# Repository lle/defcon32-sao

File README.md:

## Firmware Structure
See this readme in this repo: [SAO31](https://github.com/lle/defcon31-addon)
The foundation firmware is from my SAO from last year. This year's firmware adds an the Racing game mode in addition to the animation/screensaver mode.

## How to Flash
Things you need:
* ST-Link - I personally use an STM32F0 Nucleo Board: [497-15096-ND](https://www.digikey.ca/en/products/detail/stmicroelectronics/NUCLEO-F072RB/5047984)
* Female Connector: [H2193-ND](https://www.digikey.ca/en/products/detail/hirose-electric-co-ltd/DF13-4P-1-25DSA/241767?s=N4IgTCBcDaIBJgIwE4DMBaAcgERAXQF8g)
* Male Connector: [H2181-ND](https://www.digikey.ca/en/products/detail/hirose-electric-co-ltd/DF13-4S-1-25C/241750)
* Precrimped wires x4: [H4BXG-10112-B8-ND](https://www.digikey.ca/en/products/detail/hirose-electric-co-ltd/H4BXG-10112-B8/426117)

### Instruction
* Connect the ST-Link SWD header to the PCB's programming port

* Compile the code in STM CubeIDE: "Project"->"Build All"
* Connect your Nucleo board to your computer
* Configure the debugger as follows: "Run" -> "Debug Configurations"

* Flash the firmware: "Run" -> "Run"
* You will see this in the logs
```
Memory Programming ...
Opening and parsing file: ST-LINK_GDB_server_a15460.srec
  File          : ST-LINK_GDB_server_a15460.srec
  Size          : 21.34 KB 
  Address       : 0x08000000 
Erasing memory corresponding to segment 0:
Erasing internal memory sectors [0 21]
Download in Progress:
File download complete
Time elapsed during download operation: 00:00:01.454
Verifying ...
Download verified successfully 
Shutting down...
Exit.
```
https://github.com/lle/defcon31-addon

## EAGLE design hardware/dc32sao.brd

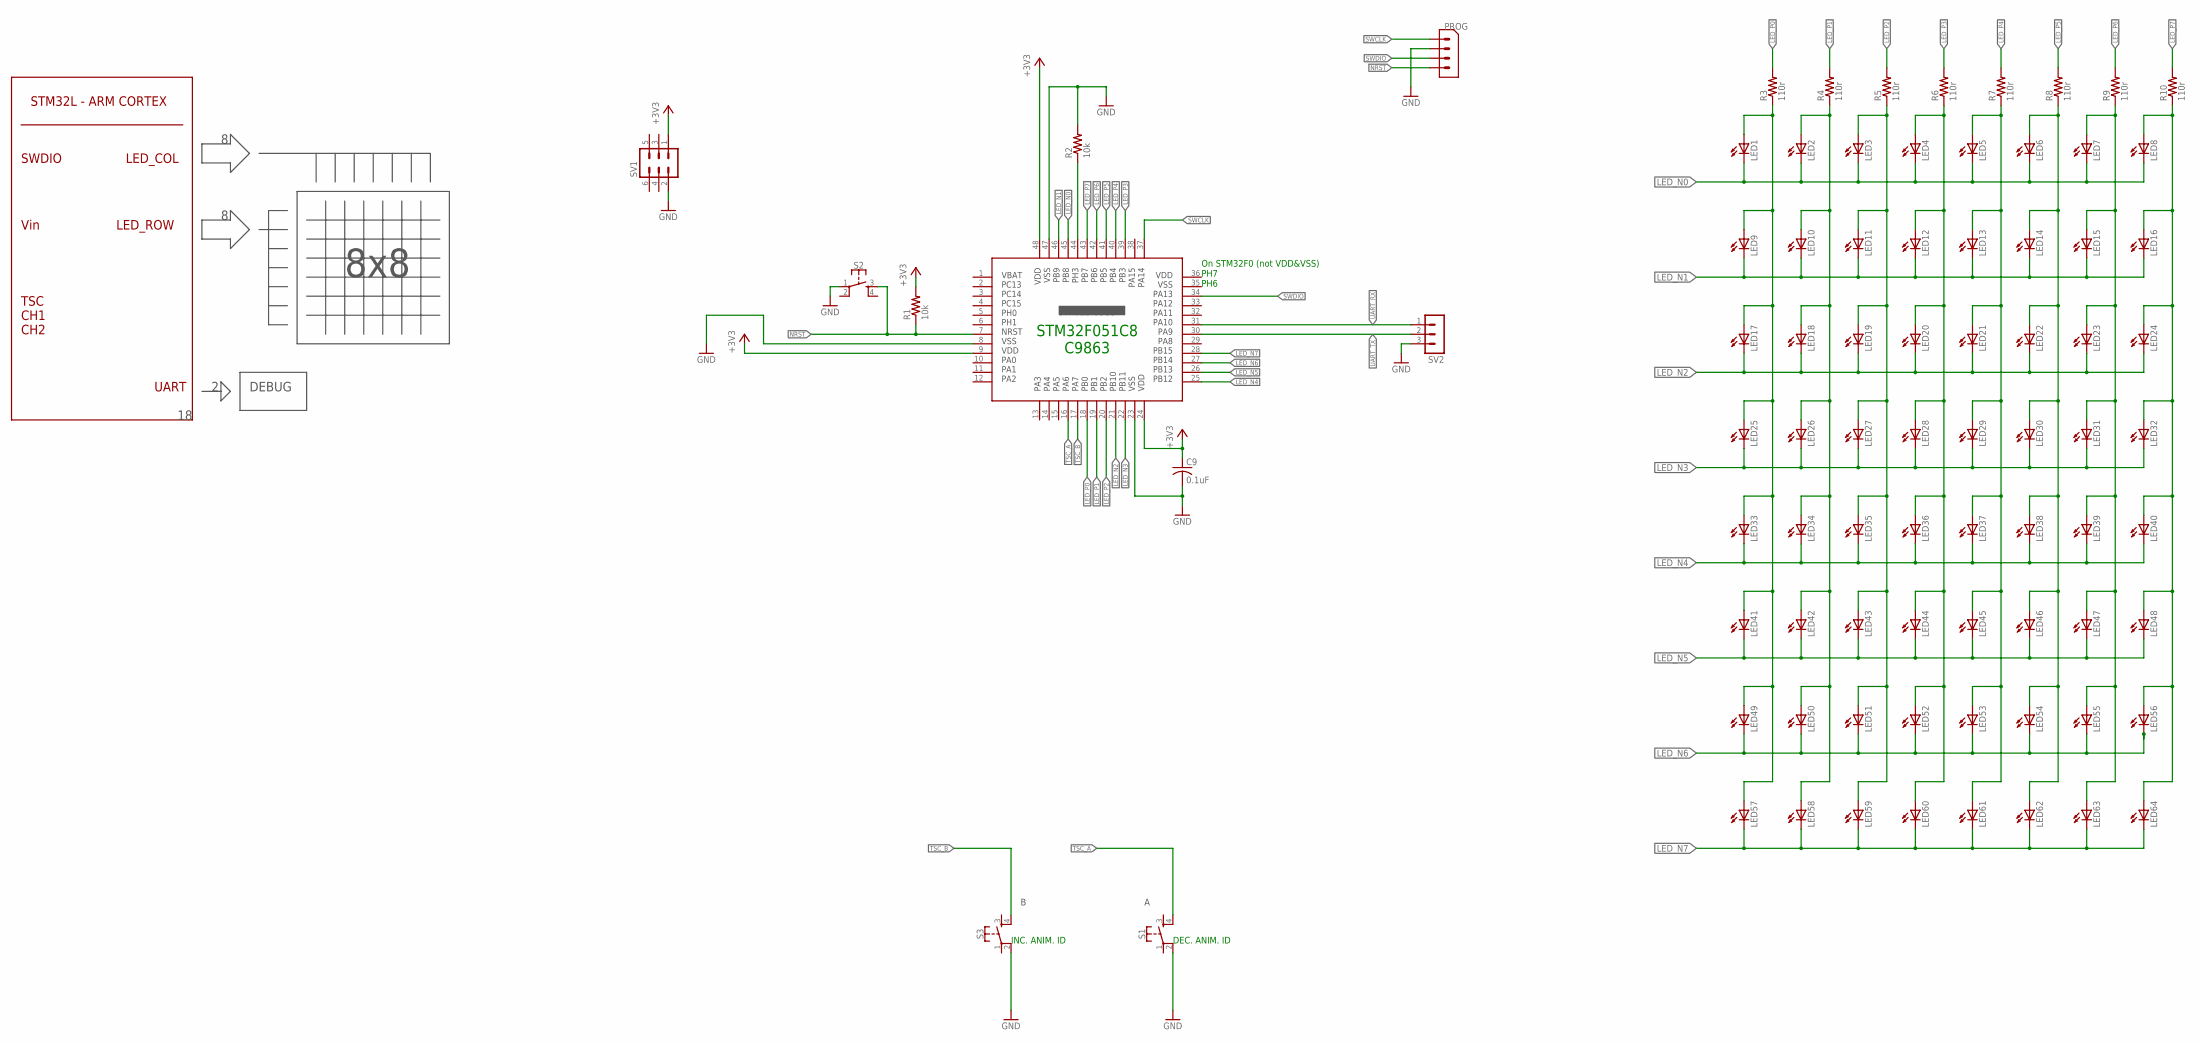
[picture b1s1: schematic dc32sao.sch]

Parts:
C9: 0.1uF; C0603
LED1, LED2, LED3, LED4, LED5, LED6, LED7, LED8, LED9, LED10, LED11, LED12, LED13, LED14, LED15, LED16, LED17, LED18, LED19, LED20, LED21, LED22, LED23, LED24, LED25, LED26, LED27, LED28, LED29, LED30, LED31, LED32, LED33, LED34, LED35, LED36, LED37, LED38, LED39, LED40, LED41, LED42, LED43, LED44, LED45, LED46, LED47, LED48, LED49, LED50, LED51, LED52, LED53, LED54, LED55, LED56, LED57, LED58, LED59, LED60, LED61, LED62, LED63, LED64: LEDCHIP-LED0603; CHIP-LED0603
PROG: 4-PIN-1.25MM
R1, R2: 10k; R0603
R3, R4, R5, R6, R7, R8, R9, R10: 110r; R0603
S1, S2, S3: MOMENTARY-SWITCH-SPST-2-SMD-5.2MM; TACTILE_SWITCH_SMD_5.2MM
SV1: MA03-2
SV2: MA03-1
U$2: STM32L431CC; QFP50P900X900X160-48

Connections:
+3V3: C9.1, R1.2, SV1.1, U$2.9, U$2.24, U$2.48
GND: C9.2, PROG.P$3 (2), R2.2, S1.2, S2.1, S3.2, SV1.2, SV2.3, U$2.8, U$2.23, U$2.47
LED_N0: LED1.C, LED2.C, LED3.C, LED4.C, LED5.C, LED6.C, LED7.C, LED8.C, U$2.45
LED_N1: LED9.C, LED10.C, LED11.C, LED12.C, LED13.C, LED14.C, LED15.C, LED16.C, U$2.46
LED_N2: LED17.C, LED18.C, LED19.C, LED20.C, LED21.C, LED22.C, LED23.C, LED24.C, U$2.21
LED_N3: LED25.C, LED26.C, LED27.C, LED28.C, LED29.C, LED30.C, LED31.C, LED32.C, U$2.22
LED_N4: LED33.C, LED34.C, LED35.C, LED36.C, LED37.C, LED38.C, LED39.C, LED40.C, U$2.25
LED_N5: LED41.C, LED42.C, LED43.C, LED44.C, LED45.C, LED46.C, LED47.C, LED48.C, U$2.26
LED_N6: LED49.C, LED50.C, LED51.C, LED52.C, LED53.C, LED54.C, LED55.C, LED56.C, U$2.27
LED_N7: LED57.C, LED58.C, LED59.C, LED60.C, LED61.C, LED62.C, LED63.C, LED64.C, U$2.28
LED_P0: R3.2, U$2.18
LED_P0B: LED1.A, LED9.A, LED17.A, LED25.A, LED33.A, LED41.A, LED49.A, LED57.A, R3.1
LED_P1: R4.2, U$2.19
LED_P1B: LED2.A, LED10.A, LED18.A, LED26.A, LED34.A, LED42.A, LED50.A, LED58.A, R4.1
LED_P2: R5.2, U$2.20
LED_P2B: LED3.A, LED11.A, LED19.A, LED27.A, LED35.A, LED43.A, LED51.A, LED59.A, R5.1
LED_P3: R6.2, U$2.39
LED_P3B: LED4.A, LED12.A, LED20.A, LED28.A, LED36.A, LED44.A, LED52.A, LED60.A, R6.1
LED_P4: R7.2, U$2.40
LED_P4B: LED5.A, LED13.A, LED21.A, LED29.A, LED37.A, LED45.A, LED53.A, LED61.A, R7.1
LED_P5: R8.2, U$2.41
LED_P5B: LED6.A, LED14.A, LED22.A, LED30.A, LED38.A, LED46.A, LED54.A, LED62.A, R8.1
LED_P6: R9.2, U$2.42
LED_P6B: LED7.A, LED15.A, LED23.A, LED31.A, LED39.A, LED47.A, LED55.A, LED63.A, R9.1
LED_P7: R10.2, U$2.43
LED_P7B: LED8.A, LED16.A, LED24.A, LED32.A, LED40.A, LED48.A, LED56.A, LED64.A, R10.1
unnamed: R2.1, U$2.44
NRST: PROG.P$1 (4), R1.1, S2.3, U$2.7
SWCLK: PROG.P$4 (1), U$2.37
SWDIO: PROG.P$2 (3), U$2.34
TSC_A: S1.4, U$2.16
TSC_B: S3.4, U$2.17
UART_RX: SV2.1, U$2.31
UART_TX: SV2.2, U$2.30

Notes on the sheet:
SWDIO
Vin
LED_COL
LED_ROW
TSC CH1 CH2
STM32L - ARM CORTEX
DEBUG
UART
8x8
STM32F051C8 C9863
On STM32F0 (not VDD&VSS) PH7 PH6
DEC. ANIM. ID
INC. ANIM. ID

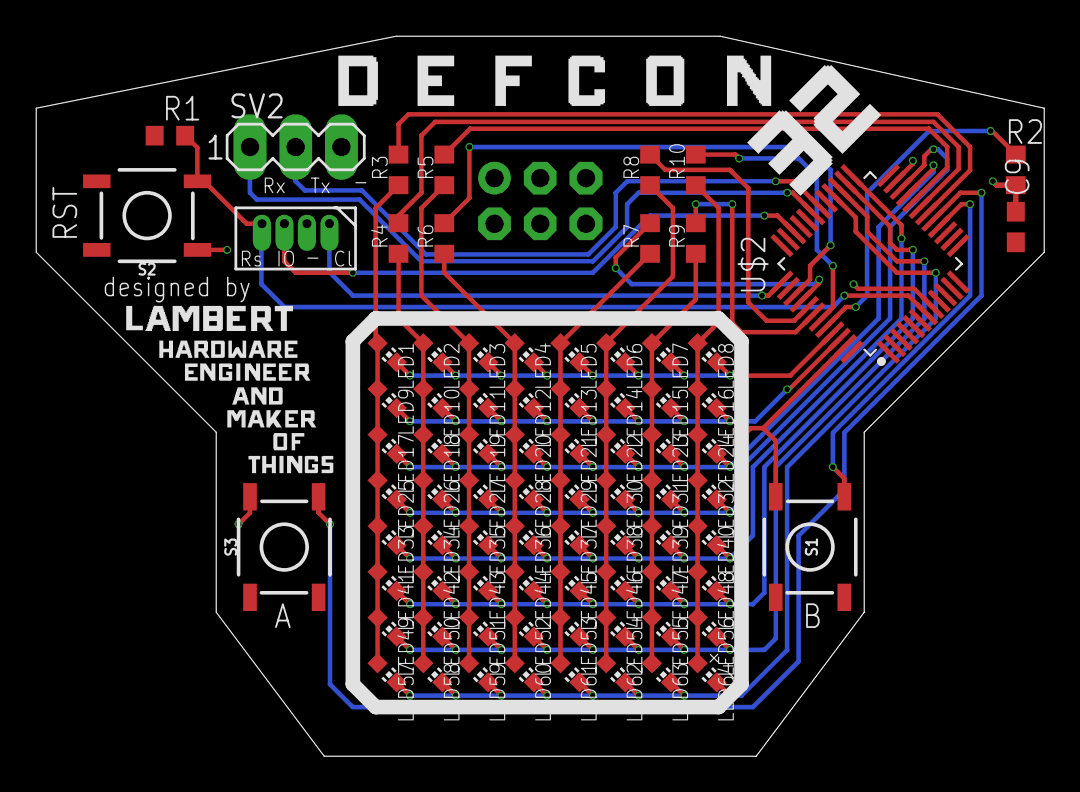
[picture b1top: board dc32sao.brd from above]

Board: 2 copper layers, 56.0 x 40.0 mm, 82 parts (1 on the bottom side), 34 nets.

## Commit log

2024-07-10 imported starting point firmware
2024-07-10 working raceCar prototype
    - todo: collision detection
    - make sure two obstacle are not side by side
2024-07-10 collision algo implemented
    todo: enabled 2nd button and map it
2024-07-11 Alpha firmware completed
    - added #define for better clarity
    - migrated to latest HAL drivers
    - added 2nd button
    - fixed edge case for collision detection during wrap around
    TODO: test on actual hardware
2024-07-22 Updated button behavior
    - animation ID starts from ZERO in the UI
    - animation start with ID = 1 ("defcon32")
    - fixed button left/right
    - added btn_a to enter into racegame during boot
2024-08-05 firmware tweaking + published hardware design
    - improved racing game behavior for better UX
    - fixed animation increment/decrement on button press
    - published the hardware design
    - added pictures assets to repo

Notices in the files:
parts and their libraries:
SparkFun-Switches: Licensing: Creative Commons ShareAlike 4.0 International - https://creativecommons.org/licenses/by-sa/4.0
